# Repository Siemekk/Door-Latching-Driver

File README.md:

# Door-Latching-Driver
Special driver for implementing the Soft Close system known from Audi, for other VAG group brands.

## PCB
PCB was full designed by my. Includes new automotive sockets for being more similar to full-comercial projects.
Program is being loaded by special ISP socket for programing. Dimension of PCB is ~62x49mm, so you can easliy put in inside Car.
PCB can be expanded to next options (For Example, closing mirrors after close Car), but I don't wanna do it, because all Cars after 2008 year, have this option in standard.

## Tests
Tests in old car (Audi A6 4F - 2006 year), was passed exactly! All things works like a new Car from 2022 year! The current consumption in sleep mode is less than <1mA, so battery is protected.
Breaking a process of latching door did not crash driver, driver wait for "full open door", and after that tries to latch it again!
In situation, where door "bowdeen cable" is broken, driver tries to latch door, but when status of door is not changed to "CLOSE", driver wait's for Open Doors, but don't REVERSE ENGINE. it's a sign to the user that something is wrong

## Assembly Instruction (Current in Polish)

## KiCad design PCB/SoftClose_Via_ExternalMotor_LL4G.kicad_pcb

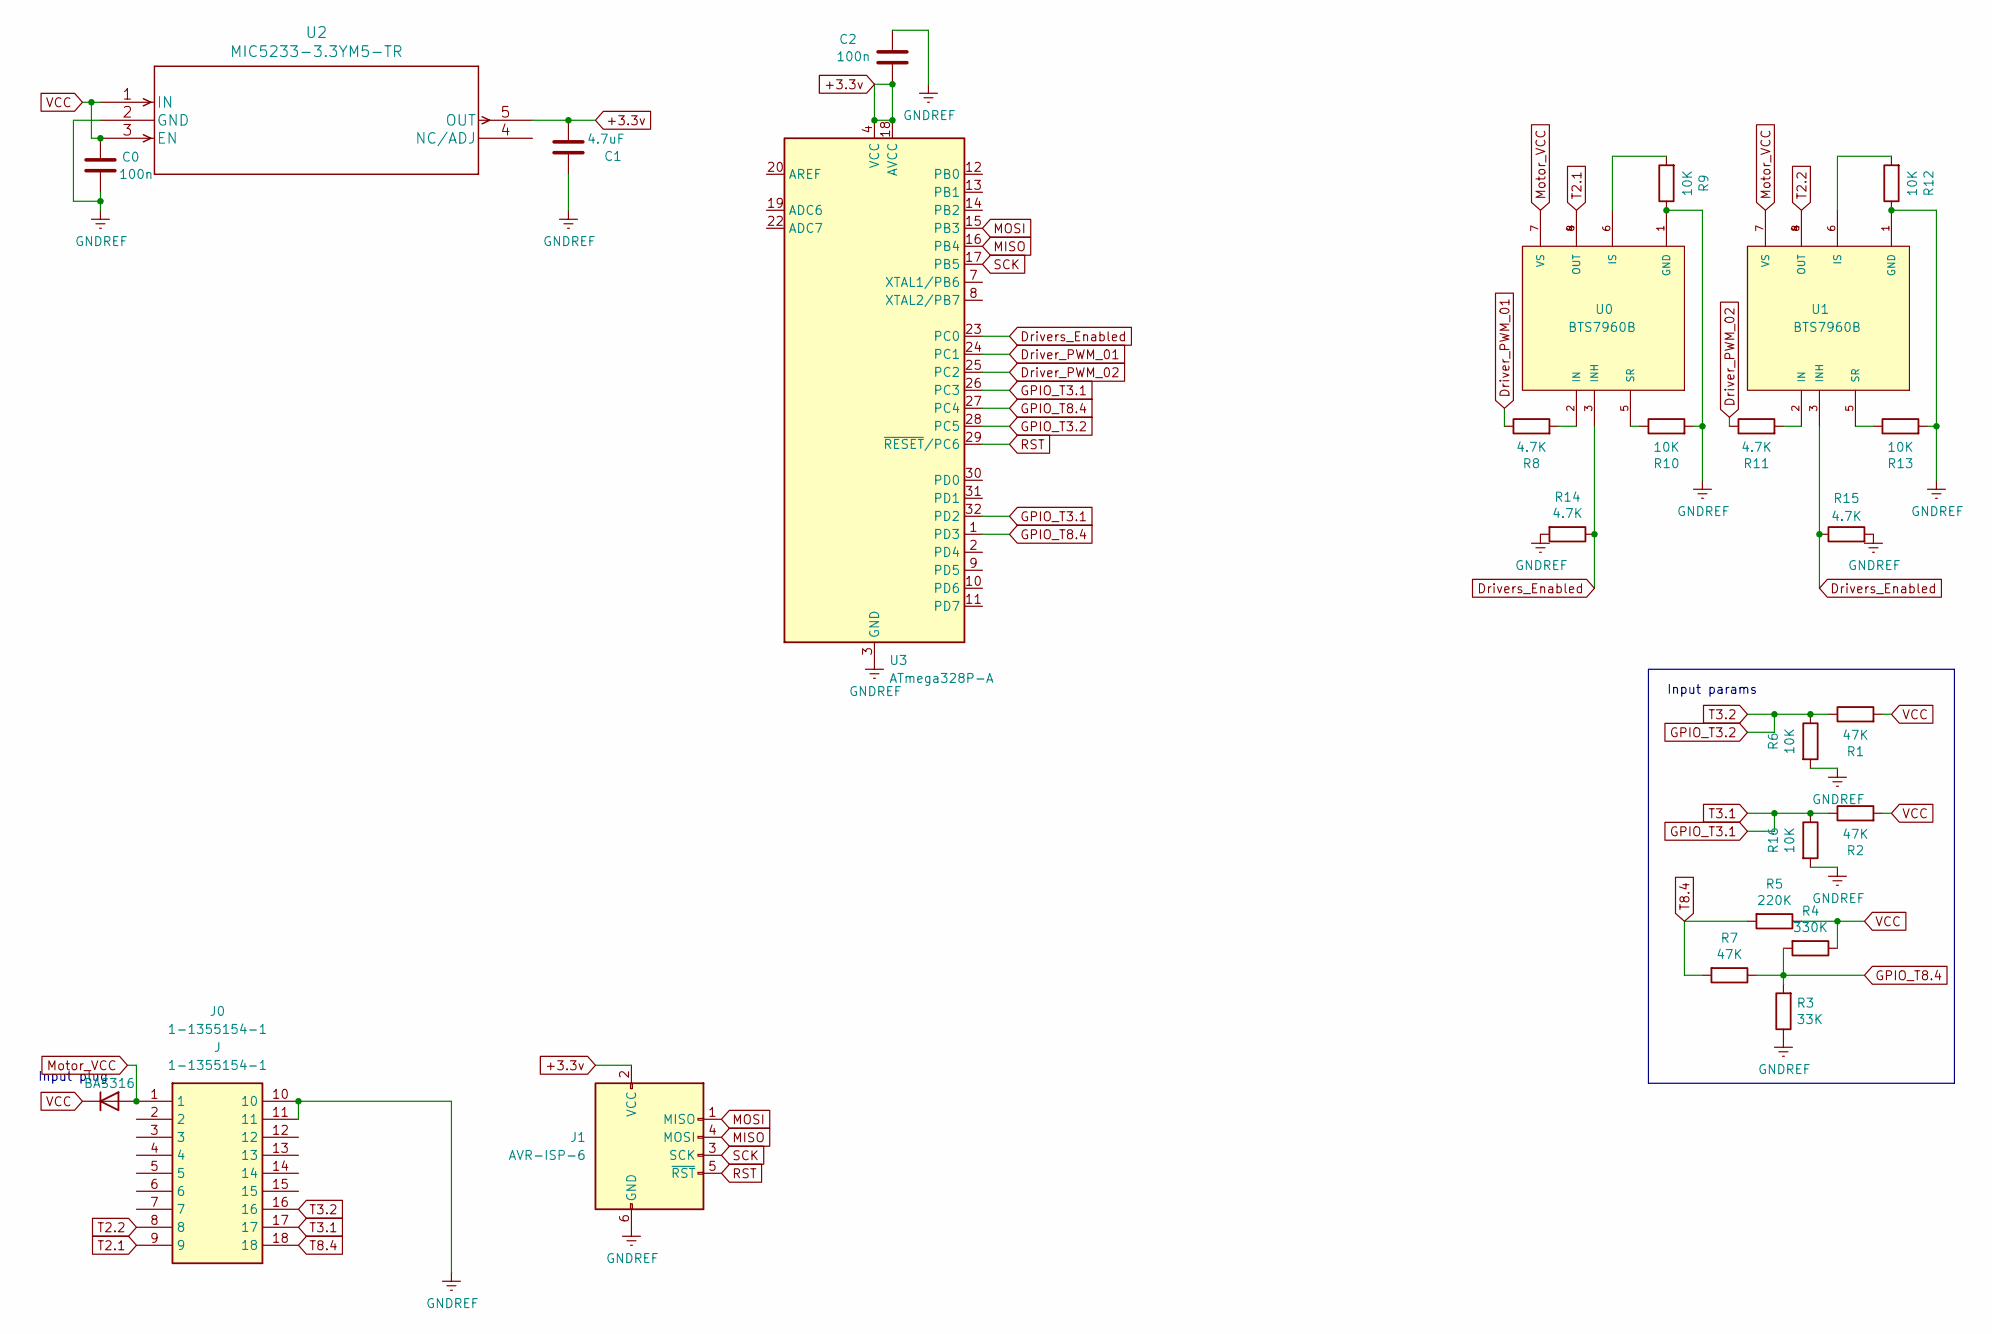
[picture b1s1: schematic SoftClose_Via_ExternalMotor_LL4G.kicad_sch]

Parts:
C0, C2: 100n; C_0603_1608Metric
C1: 4.7uF; C_0603_1608Metric
D0: BAS316; D_SOD-323
J0: 1-1355154-1; 113551541; Manufacturer_Part_Number 1-1355154-1; Mouser Part Number 571-1-1355154-1
J1: AVR-ISP-6; PinHeader_2x03_P2.54mm_Vertical
R1, R2, R7: 47K; R_0603_1608Metric
R3: 33K; R_0603_1608Metric
R4: 330K; R_0603_1608Metric
R5: 220K; R_0603_1608Metric
R6, R9, R10, R12, R13, R16: 10K; R_0603_1608Metric
R8, R11, R14, R15: 4.7K; R_0603_1608Metric
U0, U1: BTS7960B; DPAK127P1490X440-8N; PARTREV 1.1
U2: MIC5233-3.3YM5-TR
U3: ATmega328P-A; TQFP-32_7x7mm_P0.8mm

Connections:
+3.3v: C1.2, C2.2, J1.2 (VCC), U2.5 (OUT), U3.4 (VCC), U3.6 (VCC), U3.18 (AVCC)
Driver_PWM_01: R8.1, U3.24 (PC1)
Driver_PWM_02: R11.1, U3.25 (PC2)
Drivers_Enabled: R14.1, R15.1, U0.3 (INH), U1.3 (INH), U3.23 (PC0)
GPIO_T3.1: J0.17, R2.1, R16.1, U3.26 (PC3), U3.32 (PD2)
GPIO_T3.2: J0.16, R1.1, R6.1, U3.28 (PC5)
GPIO_T8.4: R3.2, R4.2, R7.1, U3.1 (PD3), U3.27 (PC4)
MISO: J1.4 (MOSI), U3.16 (PB4)
MOSI: J1.1 (MISO), U3.15 (PB3)
Motor_VCC: D0.2 (A), J0.1, U0.7 (VS), U1.7 (VS)
unnamed: R8.2, U0.2 (IN)
unnamed: R9.2, U0.6 (IS)
unnamed: R10.1, U0.5 (SR)
unnamed: R11.2, U1.2 (IN)
unnamed: R12.2, U1.6 (IS)
unnamed: R13.1, U1.5 (SR)
RST: J1.5 (~RST), U3.29 (~RESET/PC6)
SCK: J1.3 (SCK), U3.17 (PB5)
T2.1: J0.9, U0.4 (OUT), U0.8 (OUT)
T2.2: J0.8, U1.4 (OUT), U1.8 (OUT)
T8.4: J0.18, R5.2, R7.2
VCC: C0.1, D0.1 (K), R1.2, R2.2, R4.1, R5.1, U2.1 (IN), U2.3 (EN)

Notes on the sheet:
Input params
Input plug

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
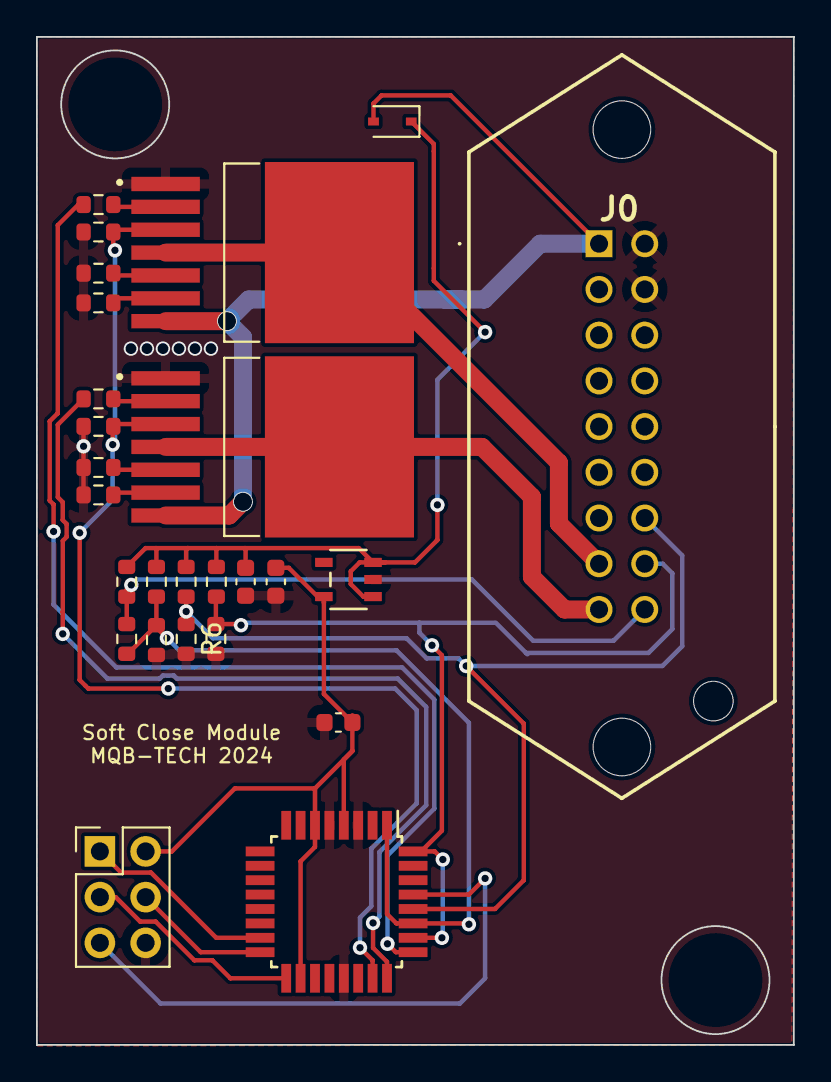
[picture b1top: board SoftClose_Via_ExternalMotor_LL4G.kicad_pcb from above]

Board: 2 copper layers, 42.0 x 56.0 mm, 26 parts (0 on the bottom side), 23 nets.

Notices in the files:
parts and their libraries:
Copyright 2016 Accelerated Designs. All rights reserved.
